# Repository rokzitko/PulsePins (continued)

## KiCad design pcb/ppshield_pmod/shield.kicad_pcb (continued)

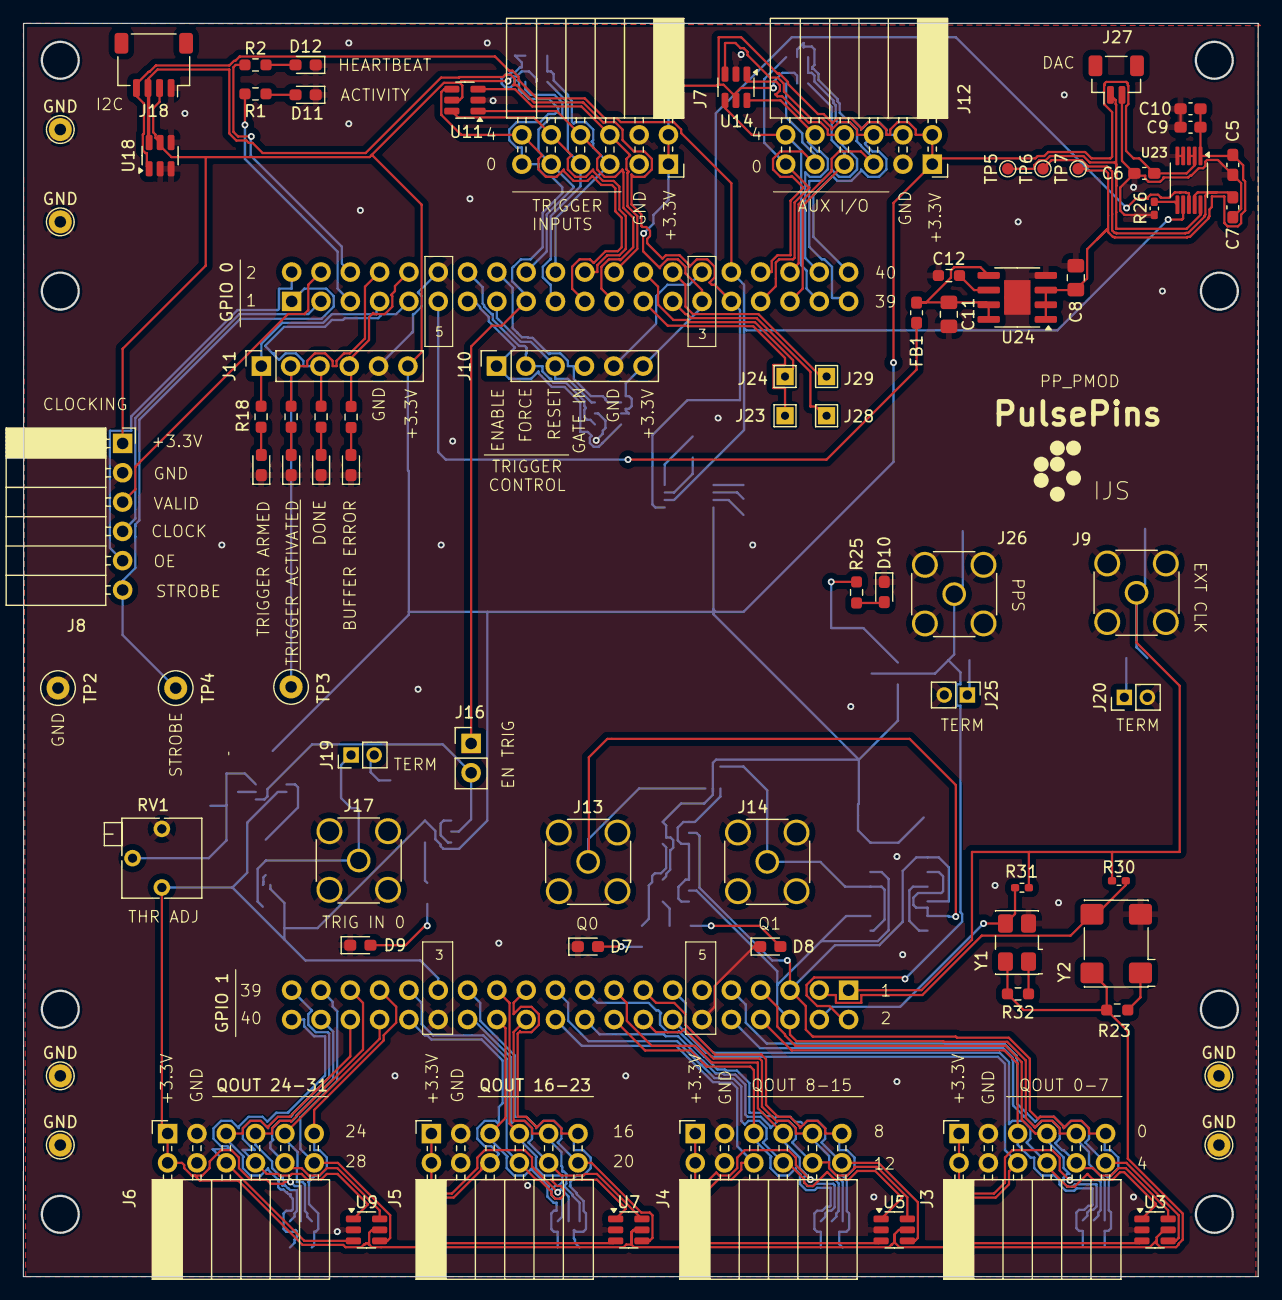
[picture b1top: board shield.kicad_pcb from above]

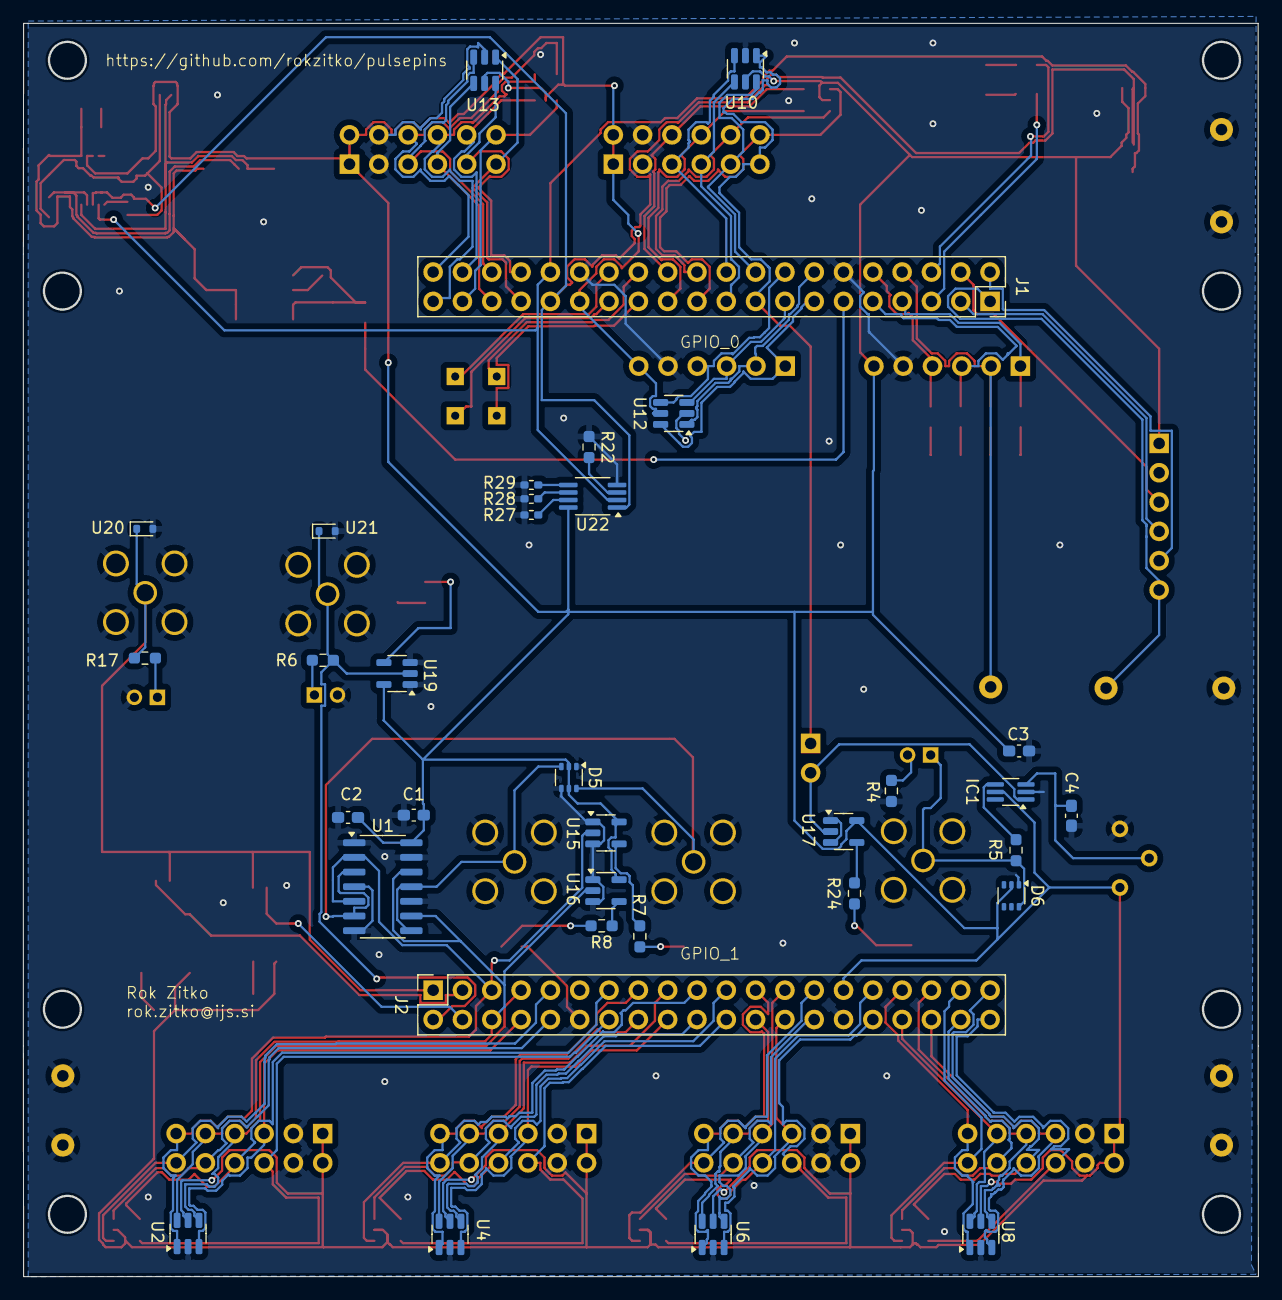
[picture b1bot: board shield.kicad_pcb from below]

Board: 2 copper layers, 107.0 x 108.6 mm, 114 parts (35 on the bottom side), 110 nets.

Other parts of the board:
GND: TestPoint; TestPoint_THTPad_D2.0mm_Drill1.0mm
GND#2, GND#3, GND#4, GND#5, GND#6: TestPoint; TestPoint_THTPad_D2.0mm_Drill1.0mm

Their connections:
GND: GND.1, GND#2.1, GND#3.1, GND#4.1, GND#5.1, GND#6.1; also elsewhere on the board

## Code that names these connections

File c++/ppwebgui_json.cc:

// SPDX-License-Identifier: MIT
// Copyright (c) 2026 Rok Zitko

#include "ppwebgui_json.hh"

#include <bitset>
#include <iomanip>
#include <sstream>

#include "combiner.hh"
#include "config.h"

namespace {

std::string bits8(const uint8_t value) {
  return std::bitset<8>(value).to_string();
}

std::string trig_bits(const uint32_t value) {
  return std::bitset<WIDTH_TRIGGER>(value & TRIGGER_MASK).to_string();
}

bool trig_enable(const uint32_t value) {
  return value & (1U << PIO1_ENABLE);
}

bool trig_force(const uint32_t value) {
  return value & (1U << PIO1_FORCE);
}

bool trig_reset(const uint32_t value) {
  return value & (1U << PIO1_RESET);
}

bool streamer_buffer_error(const uint32_t value) {
  return value & BUFFER_ERROR;
}

bool streamer_done(const uint32_t value) {
  return value & DONE;
}

bool streamer_triggered(const uint32_t value) {
  return value & TRIGGERED;
}

bool streamer_armed(const uint32_t value) {
  return value & ARMED;
}

std::string trigger_mode_to_string(const uint32_t mode) {
  switch (mode & MODE_MASK) {
  case 0: return "INT";
  case 1: return "EXT";
  case 2: return "MISC";
  case 3: return "AUX";
  case 4: return "AND";
  case 5: return "OR";
  case 6: return "XOR";
  default:
    return "UNKNOWN(" + std::to_string(mode & MODE_MASK) + ')';
  }
}

std::string trigger_mode_to_semantic_string(const TriggerConfigState &state) {
  switch (state.mode & MODE_MASK) {
  case static_cast<uint32_t>(trig_mode::INT):
    return "INT";
  case static_cast<uint32_t>(trig_mode::EXT):
    return "EXT";
  case static_cast<uint32_t>(trig_mode::MISC):
    return "MISC";
  case static_cast<uint32_t>(trig_mode::AND):
    return "ALL";
  case static_cast<uint32_t>(trig_mode::OR):
    return "ANY";
  default:
    return trigger_mode_to_string(state.mode);
  }
}

} // namespace

std::string json_escape(std::string_view input) {
  std::ostringstream out;
  for (const auto ch : input) {
    switch (ch) {
    case '\\': out << "\\\\"; break;
    case '"': out << "\\\""; break;
    case '\b': out << "\\b"; break;
    case '\f': out << "\\f"; break;
    case '\n': out << "\\n"; break;
    case '\r': out << "\\r"; break;
    case '\t': out << "\\t"; break;
    default:
      if (static_cast<unsigned char>(ch) < 0x20) {
        out << "\\u"
            << std::hex << std::uppercase << std::setw(4) << std::setfill('0')
            << static_cast<unsigned>(static_cast<unsigned char>(ch))
            << std::dec << std::nouppercase << std::setfill(' ');
      } else {
        out << ch;
      }
      break;
    }
  }
  return out.str();
}

std::string status_to_json(const StatusSnapshot &status) {
  std::ostringstream out;
  out << '{';
  out << "\"seqno\":" << status.seqno << ',';
  out << "\"poll_ms\":" << status.poll_ms << ',';
  out << "\"aux\":{";
  out << "\"raw\":" << static_cast<unsigned>(status.aux_raw) << ',';
  out << "\"bits\":\"" << bits8(status.aux_raw) << "\"},";
  out << "\"trig\":{";
  out << "\"raw\":" << status.trig_raw << ',';
  out << "\"bits\":\"" << trig_bits(status.trig_raw) << "\",";
  out << "\"enable\":" << (trig_enable(status.trig_raw) ? "true" : "false") << ',';
  out << "\"force\":" << (trig_force(status.trig_raw) ? "true" : "false") << ',';
  out << "\"reset\":" << (trig_reset(status.trig_raw) ? "true" : "false") << "},";
  out << "\"trigger_settings\":{";
  out << "\"mode\":\"" << trigger_mode_to_semantic_string(status.trigger_settings) << "\",";
  out << "\"invert_result\":" << status.trigger_settings.invert_result << ',';
  out << "\"invert_int\":" << status.trigger_settings.invert_int << ',';
  out << "\"invert_ext\":" << status.trigger_settings.invert_ext << ',';
  out << "\"invert_misc\":" << status.trigger_settings.invert_misc << ',';
  out << "\"invert_aux\":" << status.trigger_settings.invert_aux << ',';
  out << "\"mask_int\":" << status.trigger_settings.mask_int << ',';
  out << "\"mask_ext\":" << status.trigger_settings.mask_ext << ',';
  out << "\"mask_misc\":" << status.trigger_settings.mask_misc << ',';
  out << "\"mask_aux\":" << status.trigger_settings.mask_aux << "},";
  out << "\"clocking\":{";
  out << "\"tracked\":{";
  out << "\"source\":\"" << (status.clocking.tracked.source_managed ? json_escape(status.clocking.tracked.source_display) : "unmanaged") << "\",";
  out << "\"source_display\":\"" << json_escape(status.clocking.tracked.source_display) << "\",";
  out << "\"source_managed\":" << (status.clocking.tracked.source_managed ? "true" : "false") << ',';
  out << "\"core_profile\":\"" << json_escape(status.clocking.tracked.core.profile) << "\",";
  out << "\"int_profile\":\"" << json_escape(status.clocking.tracked.internal.profile) << "\"},";
  out << "\"measured\":{";
  out << "\"ext_clk_hz\":" << status.clocking.measured.ext_clk_hz << ',';
  out << "\"int_clk_hz\":" << status.clocking.measured.int_clk_hz << ',';
  out << "\"streamer_clk_hz\":" << status.clocking.measured.streamer_clk_hz << ',';
  out << "\"core_clk_hz\":" << status.clocking.measured.core_clk_hz << "}},";
  out << "\"stream\":{";
  out << "\"last_rc\":" << status.last_stream_rc << ',';
  out << "\"message\":\"" << json_escape(status.stream_message) << "\",";
  out << "\"runtime\":{";
  out << "\"raw\":" << status.streamer.status_raw << ',';
  out << "\"buffer_error\":" << (streamer_buffer_error(status.streamer.status_raw) ? "true" : "false") << ',';
  out << "\"done\":" << (streamer_done(status.streamer.status_raw) ? "true" : "false") << ',';
  out << "\"triggered\":" << (streamer_triggered(status.streamer.status_raw) ? "true" : "false") << ',';
  out << "\"armed\":" << (streamer_armed(status.streamer.status_raw) ? "true" : "false") << "}},";
  out << "\"streamer\":{";
  out << "\"status_raw\":" << status.streamer.status_raw << ',';
  out << "\"qout\":" << status.streamer.qout << ',';
  out << "\"qout_streamer\":" << status.streamer.qout_streamer << ',';
  out << "\"override\":{";
  out << "\"enabled\":" << (status.streamer.override_state.enabled ? "true" : "false") << ',';
  out << "\"value\":" << status.streamer.override_state.value << "}},";
  out << "\"combiner\":{";
  out << "\"mode\":\"" << status.combiner_mode << "\",";
  out << "\"output\":{";
  out << "\"invert\":" << status.output.invert << ',';
  out << "\"mask\":" << status.output.mask << ',';
  out << "\"force_enabled\":" << (status.output.force_enabled ? "true" : "false") << ',';
  out << "\"force_value\":" << status.output.force_value << "},";
  out << "\"inputs\":[";
  for (size_t i = 0; i < status.inputs.size(); ++i) {
    const auto &input = status.inputs[i];
    if (i) out << ',';
    out << '{';
    out << "\"index\":" << (i + 1) << ',';
    out << "\"invert\":" << input.invert << ',';
    out << "\"mask\":" << input.mask << ',';
    out << "\"force_enabled\":" << (input.force_enabled ? "true" : "false") << ',';
    out << "\"force_value\":" << input.force_value;
    out << '}';
  }
  out << "]},";
  out << "\"last_action\":\"" << json_escape(status.last_action) << "\",";
  out << "\"last_error\":\"" << json_escape(status.last_error) << "\"";
  out << '}';
  return out.str();
}

std::string operation_json(const std::string &message, const StatusSnapshot &status, const int rc) {
  std::ostringstream out;
  out << '{';
  out << "\"ok\":true,";
  out << "\"rc\":" << rc << ',';
  out << "\"message\":\"" << json_escape(message) << "\",";
  out << "\"status\":" << status_to_json(status);
  out << '}';
  return out.str();
}

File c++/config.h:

// SPDX-License-Identifier: MIT
// Copyright (c) 2025 Rok Zitko

// Constants

#pragma once

#include <cstddef>
#include <cstdint>
#include <limits>

#include "misc.hh"

constexpr int P_FIFO_IN1 = 10;
constexpr int P_FIFO_IN2 = 11;
constexpr int P_FIFO_OUT = 12;
constexpr int SIZE_FIFO_IN1 = 1 << P_FIFO_IN1;
constexpr int SIZE_FIFO_IN2 = 1 << P_FIFO_IN2;
constexpr int SIZE_FIFO_OUT = 1 << P_FIFO_OUT;
constexpr int almost_shift = 16; // see input_fifo.sv

constexpr int WIDTH_AVS_BUS = 32; // port width of the AVS bus used in the streaming interface
using bus_t = uint32_t;           // corresponding C++ type
constexpr int WIDTH_PORT = 32;    // port width in bits for various FPGA interfaces
using port_t = uint32_t;          // corresponding C++ type

static_assert(sizeof(bus_t)*8 == WIDTH_AVS_BUS);
static_assert(sizeof(port_t)*8 == WIDTH_PORT);

// These must be consistent with ip/streamer/config.vh

constexpr int WIDTH_CONTROL = 32;
constexpr int WIDTH_COUNTER = 32;
constexpr int WIDTH_DATA = 32;
constexpr int WIDTH_TOTAL = WIDTH_CONTROL + WIDTH_COUNTER + WIDTH_DATA;
constexpr int BYTES_TOTAL = WIDTH_TOTAL/8;

using control_t = uint32_t; // control register data type
using count_t   = uint32_t; // counter register data type
using value_t   = uint32_t; // value data type

static_assert(sizeof(control_t)*8 == WIDTH_CONTROL);
static_assert(sizeof(count_t)*8   == WIDTH_COUNTER);
static_assert(sizeof(value_t)*8   == WIDTH_DATA);

const uint64_t max_count_t = std::numeric_limits<count_t>::max(); // for checking boundaries

using trigger_t = uint8_t;
constexpr int WIDTH_TRIGGER = 8;
constexpr int TRIGGER_MASK = 0xFF;

using aux_t = uint8_t;
constexpr int WIDTH_AUX = 8;
constexpr int AUX_MASK = 0xFF;

constexpr uint32_t CFG_STREAMER_ACTIVE_MASK_OFFSET = 13;
constexpr uint32_t CFG_STREAMER_ARMED_LIVE_MASK_OFFSET = 17;
constexpr uint32_t STREAMER_MASK_BITS = 4;
constexpr uint32_t STREAMER_MASK_VALUE_MASK = 0x0f;
constexpr uint32_t STREAMER_ACTIVE_MASK_CFG_MASK =
  STREAMER_MASK_VALUE_MASK << CFG_STREAMER_ACTIVE_MASK_OFFSET;
constexpr uint32_t STREAMER_ARMED_LIVE_MASK_CFG_MASK =
  STREAMER_MASK_VALUE_MASK << CFG_STREAMER_ARMED_LIVE_MASK_OFFSET;

// Function aliases; we need two sets due to different interfaces (_t versions accept
// a string; those without _t suffix accept InputParse, keyword, default_value)
const auto parse_value_t = parse_uint32_t;
const auto parse_count_t = parse_uint32_t;
const auto parse_trigger_t = parse_uint8_t;
const auto parse_value = parse_uint32;
const auto parse_count = parse_uint32;
const auto parse_trigger = parse_uint8;

constexpr int PIO1_ENABLE = 8;
constexpr int PIO1_FORCE  = 9;
constexpr int PIO1_RESET  = 10;

static_assert(sizeof(trigger_t)*8 == WIDTH_TRIGGER);

// control (least significant bits):
//        0 - regular element [bit 0]
//        1 - trigger element
//       01 - trigger element (part of the sequence) [bit 1]
//       11 - trigger element (last in the sequence)
//      1x0 - sequence terminator (subtype of regular data) [bit 2]
//     1xx0 - pulses without strobes [bit 3]
// 0000xxx0 - load word [bits 4-7]
// 0001xxx0 - bit set (for bit addressing)
// 0010xxx0 - bit clear (for bit addressing)
// 0011xxx0 - bit flip (for bit addressing)
// [bit 8]  - 0=pass, 1=discard/store/replay
// [bit 9]  - store
// [bit 15] - replay
// [bit 16] - retrig
// [bit 17] - random

// These must be consistent with ip/streamer/config.vh
constexpr control_t STROBE       = 0b0000;
constexpr control_t TRIGGERBITS  = 0b0011; // mask for testing the trigger condition
constexpr control_t TRIGGER      = 0b0001;
constexpr control_t TRIGGERFINAL = 0b0010;
constexpr control_t TERMINATE    = 0b0100;
constexpr control_t NOSTROBE     = 0b1000;

constexpr control_t MODEBITS     = 0b1111'0000; // mask for testing the update mode

constexpr control_t BITLOAD      = 0b0000'0000;
constexpr control_t BITSET       = 0b0001'0000;
constexpr control_t BITCLEAR     = 0b0010'0000;
constexpr control_t BITFLIP      = 0b0011'0000;

constexpr control_t BITNOT       = 0b0100'0000;
constexpr control_t BITAND       = 0b0101'0000;
constexpr control_t BITOR        = 0b0110'0000;
constexpr control_t BITXOR       = 0b0111'0000;
constexpr control_t BITXNOR      = 0b1000'0000;

constexpr control_t BITSLL       = 0b1001'0000;
constexpr control_t BITSRL       = 0b1010'0000;

constexpr control_t PASS         = 0;
constexpr control_t NOPASS       = (1UL << 8);
constexpr control_t DISCARD      = NOPASS;
constexpr control_t STORE        = NOPASS + (1UL << 9);
constexpr control_t REPLAY       = NOPASS + (1UL << 15);
constexpr control_t RETRIG       = (1UL << 16);
constexpr control_t PRNG         = (1UL << 17);

constexpr size_t POSITIONS = 8; // number of elements that can be stored in fast memory
constexpr size_t SHIFT_POSITION = 10;
constexpr control_t POSITIONS_MASK = (0b111UL << SHIFT_POSITION);

// This must be consistent with ip/streamer/config.vh
constexpr port_t IF_CTRL       = 0b00000;
constexpr port_t INIT_VAL      = 0b00100;
constexpr port_t QOUT_OVERRIDE = 0b00110;
constexpr port_t GATING_W      = 0b00111;

constexpr port_t IF_STATUS     = 0b00000;
constexpr port_t EXT_TRIG_IN   = 0b00001;
constexpr port_t QOUT_STREAMER = 0b00010;
constexpr port_t EXT_TRIG_CTRL = 0b00011;
constexpr port_t QOUT          = 0b00100;
constexpr port_t FIFO_OVERFLOW = 0b00101;
constexpr port_t CRC32         = 0b00110;
constexpr port_t GATING_R      = 0b00111;

constexpr port_t INPUT_FIFO1_CTR_IN_L  = 0b01000;
constexpr port_t INPUT_FIFO1_CTR_IN_H  = 0b01001;
constexpr port_t INPUT_FIFO1_CTR_OUT_L = 0b01010;
constexpr port_t INPUT_FIFO1_CTR_OUT_H = 0b01011;
constexpr port_t INPUT_FIFO2_CTR_IN_L  = 0b01100;
constexpr port_t INPUT_FIFO2_CTR_IN_H  = 0b01101;
constexpr port_t INPUT_FIFO2_CTR_OUT_L = 0b01110;
constexpr port_t INPUT_FIFO2_CTR_OUT_H = 0b01111;
constexpr port_t OUTPUT_FIFO_CTR_IN_L  = 0b10000;
constexpr port_t OUTPUT_FIFO_CTR_IN_H  = 0b10001;
constexpr port_t OUTPUT_FIFO_CTR_OUT_L = 0b10010;
constexpr port_t OUTPUT_FIFO_CTR_OUT_H = 0b10011;

static_assert(GATING_W == GATING_R);

// Sanity tests
static_assert((TRIGGERBITS & TRIGGER)      == TRIGGER);
static_assert((TRIGGERBITS & TRIGGERFINAL) == TRIGGERFINAL);
static_assert((MODEBITS & BITLOAD)  == BITLOAD);
static_assert((MODEBITS & BITSET)   == BITSET);
static_assert((MODEBITS & BITCLEAR) == BITCLEAR);
static_assert((MODEBITS & BITFLIP)  == BITFLIP);

// must be consistent with ip/streamer/st_interface.sv
// status bits
constexpr port_t BUFFER_ERROR = 0x01;
constexpr port_t DONE         = 0x02;
constexpr port_t TRIGGERED    = 0x04;
constexpr port_t ARMED        = 0x08;

// control bits
constexpr port_t STOP                 = 0x01;
constexpr port_t TRIGGER_FORCE_INT    = 0x02;
constexpr port_t TRIGGER_ENABLE_INT   = 0x04;
constexpr port_t RESET                = 0x08;
constexpr port_t TRIGGER_RESET_INT    = 0x10;
constexpr port_t QOUT_SELECT          = 0x20;
constexpr port_t STOP_ON_BUFFER_ERROR = 0x40;

// bit masks for EXT_TRIG_CTRL
constexpr port_t EXT_TRIG_CTRL_ENABLE = 1<<0;
constexpr port_t EXT_TRIG_CTRL_FORCE  = 1<<1;
constexpr port_t EXT_TRIG_CTRL_RESET  = 1<<2;

// bit masks for TRIG_CTRL when combined with other signals (in combiner)
constexpr port_t TRIG_CTRL_ENABLE = 1<<(WIDTH_TRIGGER+0);
constexpr port_t TRIG_CTRL_FORCE  = 1<<(WIDTH_TRIGGER+1);
constexpr port_t TRIG_CTRL_RESET  = 1<<(WIDTH_TRIGGER+2);

// Final value when streaming terminates
constexpr value_t default_final_value = 0xFFFFFFFF;

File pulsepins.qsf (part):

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#set_location_assignment PIN_Y15 -to GPI1GPIO[0]
set_location_assignment PIN_Y15 -to EXT_CLKp
#set_location_assignment PIN_AC24 -to GPI1GPIO[1]
set_location_assignment PIN_AC24 -to PPS_IN
#set_location_assignment PIN_AA15 -to GPI1GPIO[2]
set_location_assignment PIN_AA15 -to PPCLK1
#set_location_assignment PIN_AD26 -to GPI1GPIO[3]
set_location_assignment PIN_AD26 -to PPCLK2
set_location_assignment PIN_AG28 -to GPI1Q[0] # GPI1GPIO[4]...
set_location_assignment PIN_AF28 -to GPI1Q[1]
set_location_assignment PIN_AE25 -to GPI1Q[2]
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
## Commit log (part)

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2026-04-04 path to pp for Python
2026-04-04 generalize file playback with ppplay
2026-04-04 enable binary playback and quiet parser errors
2026-04-04 standardize readback export option names
2026-04-04 prefer ppplay in docs and tests
2026-04-04 add ppplay text and binary tests
2026-04-04 document ip testbench purpose
2026-04-04 add streamer underrun testbench
2026-04-04 add streamer trigger replay test
2026-04-04 expand Python binding smoke coverage
2026-04-04 integrate counter testbenches into IP regressions
2026-04-05 installation fixes
2026-04-05 Makefile cleanup
2026-04-06 I2C OLED display test
2026-04-07 Fix ppwebgui stream playback path
2026-04-08 Return ppwebgui status in POST replies
2026-04-08 Print ppwebgui interface URLs on startup
2026-04-08 Add ppwebgui stop control
2026-04-08 ppwebgui
2026-04-08 Fix ppwebgui stream status locking
2026-04-08 Debug ppwebgui stream lock crash
2026-04-08 Externalize ppwebgui stream debug state
2026-04-08 Stabilize ppwebgui stream startup
2026-04-08 Use global stream state in ppwebgui
2026-04-08 Build ppwebgui without inlining
2026-04-08 Simplify ppwebgui verbose action logging
2026-04-08 Simplify ppwebgui to synchronous control
2026-04-08 Use local qout wrappers in ppwebgui
2026-04-09 cleanup to suppress warnings
2026-04-09 tracing support
2026-04-09 HW_DEBUG
2026-04-09 get_loc -> get_addr
2026-04-10 cleanup
2026-04-11 experimental support for updating outputs at both clock edges (DDR)
2026-04-11 give ppwebgui a fresh reset before each stream
    Run the existing bring-up path before browser-triggered streaming so each launch starts from a clean hardware state. Keep the deterministic final qout behavior aligned with the manual reset flow.
2026-04-11 clarify ppwebgui live vs tracked interface state
    Split the browser UI into live-hardware and ppwebgui-tracked sections so snapshot-backed values stop reading like live hardware state. Surface unapplied local edits in the override and combiner forms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
2026-04-12 add shared ppwebgui value type definitions
    Introduce a dedicated header for the value structs shared across ppwebgui so later separation work can stop mixing request/status data models with the rest of the web server implementation.
2026-04-12 add stable ppwebgui service interface adapter
    Route ppwebgui through a value-based service interface without moving or re-owning the hardware controller object. Keep the WebGuiController instance anchored in main and let the adapter hold only a 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
2026-04-12 extract ppwebgui json presentation helpers
    Move JSON encoding and status presentation helpers out of ppwebgui.cc so response rendering can evolve independently of the main server/bootstrap file. Keep the HTTP behavior and hardware-control own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
2026-04-12 split ppwebgui runtime config from input parsing
    Resolve ppwebgui startup and policy settings into a pure WebGuiRuntimeConfig in main, then pass that config into the anchored controller instead of storing the raw InputParser. Keep the hardware-owni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
2026-04-12 extract ppwebgui app composition
    Move the ppwebgui composition block out of the main file while keeping the hardware-owning controller anchored as a direct local in the app runner. This keeps ppwebgui.cc focused on process entry and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
2026-04-12 decouple ppwebgui app runner from host runtime
    Resolve the pure WebGuiRuntimeConfig in ppwebgui_main.cc and pass only FPGA, Verbosity, and the resolved config into the app runner. Keep the hardware controller anchored in the app layer while remov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
2026-04-12 make ppwebgui server depend on explicit assets
    Pass a pure WebGuiAssets bundle from the app layer into the server runner so the server module no longer reaches into asset globals directly. This keeps the controller lifetime unchanged while making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
2026-04-12 centralize ppwebgui frontend boundary types
    Collect the remaining pure GUI/server boundary structs into a single frontend header and update the server and HTTP layers to consume those values explicitly. Refresh the maintainer docs so the final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
2026-04-12 document final ppwebgui architecture split
    Update the maintainer docs to reflect the completed ppwebgui layering, control flow, and pure-value boundaries between the app, server, HTTP, and hardware-owning service layers. Record the anchored W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
2026-04-12 add backend trigger updates for ppwebgui
    Add a pure trigger configuration request type, service/controller apply path, and POST /api/trigger so ppwebgui can update trigger settings through the split backend architecture. Preserve AUX trigge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
2026-04-12 document editable trigger settings in ppwebgui
    Update the ppwebgui docs to describe the new trigger editing flow, the semantic trigger modes exposed in the browser, and the POST /api/trigger endpoint. Clarify that AUX trigger fields remain visibl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
2026-04-13 add ppwebgui clocking controls
    Expose tracked clock source and PLL profile settings in the browser, along with measured ext/int/streamer/core frequency snapshots and a remeasure action. Reuse the existing dirty/apply/revert form b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
2026-04-13 fix clocking + reduce verbosity
2026-04-13 harden ppscpi session handling and shutdown semantics
    Contain SCPI handler exceptions inside the generic session layer so malformed or failing commands stop affecting only the current request instead of tearing down the whole server. Add explicit DISCON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
2026-04-15 harden host startup and input parsing
    Reject malformed numeric arguments deterministically, fail fast on invalid raw clock selection, and surface startup compatibility errors instead of relying on asserts or uncaught exceptions.
2026-04-16 fix RC codes to make them unique
2026-04-16 sh -> bash
2026-04-17 harden timeout handling and web recovery
2026-04-17 add AD9833 SPI payload target
    Split the standalone SPI payload generator around a shared 32-bit encoder so the new 5 MHz AD9833 sequence can drive qout[16..19] without breaking the existing PMODDA3 binary.
2026-04-17 add AD9833 amplifier payload target
    Add an MCP41010 helper and a third spi_payload binary so the DollaTek module can be programmed for the same 5 MHz AD9833 setup plus the board's approximate 5x amplified-output stage from one generate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
2026-04-17 flatten element storage
    Store raw control/count/value fields inside el instead of shared wrapper objects while preserving the existing constructor surface and semantic behavior covered by the unit tests.
2026-04-17 sync element mode metadata
    Replace RTTI-based wrapper classification with explicit kind tags and resynchronize cached regular-mode semantics when control bits change, backed by regression tests for setter behavior.
2026-04-17 share element control decoding
    Centralize raw control-word and trigger-field decoding in el so binary reconstruction and text serialization reuse the same helper logic, with regression tests covering the shared decoders.
2026-04-17 add immutable element transforms
    Replace the last setter choreography with immutable el helpers, derive element kind from control, and centralize regular token parsing so sequence reconstruction and text conversion share the same ru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
2026-04-20 align Python element bindings
    Update the Python bindings, tests, and docs to the flattened el API, add the missing retrig/prng surface, and make the board-side test fixture tolerate frequency-meter layouts that do not expose the 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
2026-04-20 tighten include hygiene
    Add missing direct includes and drop clearly unused ones in the audited project-owned C++ sources so core headers, tools, and bindings rely less on transitive includes.
2026-04-20 hps_0.h for CI
2026-04-20 pregenerated hps_0.h
2026-04-20 one more
2026-04-20 add worked examples guide
    Replace the examples roadmap with concrete PulsePins workflows that show exact commands, expected behavior, and links to the detailed tool pages for common bring-up and lab tasks.
2026-04-20 add extension cookbook
    Document the concrete file-by-file extension paths for new CLI tools, Python bindings, sequence constructs, tests, and ppwebgui features so contributors can add functionality without reverse-engineer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
2026-04-20 split Python bindings across translation units
2026-04-20 fix exclusion
2026-04-21 add board smoke automation
2026-04-21 expand board smoke failure coverage
2026-04-21 report ppscpi failures in error queue
2026-04-22 polish docs landing and dev workflow
    Turn the docs front door into a hardware-first guide, upgrade the weakest command pages, add a unified host-side dev-check target, and align CI and testing docs around dev-check, board-smoke, and run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
2026-04-29 add option to skip forever test reports
2026-04-29 add browser timeline composer
2026-04-30 add timeline draft import export
2026-04-30 add timeline preview click insertion
2026-04-30 add timeline pulse selection controls
2026-04-30 add timeline selection keyboard shortcuts
2026-04-30 list ppwebgui interface addresses
2026-04-30 add host-side timeline builder
2026-04-30 add timeline draft json roundtrip
2026-04-30 add ppscpi clock workflow helpers
2026-05-23 rstmgr as part of class fpga
2026-05-26 dark_mode
2026-06-05 move version check into FPGA
2026-06-05 fix servo PWM duty units
2026-06-06 fix ppfreq sample count
2026-06-06 use RAII cout locking
2026-06-06 replace runtime asserts with exceptions
2026-06-06 add loc address constructors
2026-06-06 make random final output explicit
2026-06-06 validate numeric timing inputs
2026-06-06 avoid narrowing ppfreq count
2026-06-07 gate quartus timing checks
2026-06-07 refresh ppfreq streamer clock cache
2026-06-07 hide inactive readback mode
2026-06-07 remove stale ppwebgui workaround note
2026-06-07 resolve quartus tools from qdir
2026-06-07 cover omitted ip test benches
2026-06-07 document rtl latency behavior
2026-06-07 clarify reset behavior in docs
2026-06-07 fix qsys component dependencies
2026-06-07 clean third party c++ artifacts
2026-06-07 update timestamp timeout test
2026-06-23 standardize return codes
2026-06-23 refresh tool documentation
2026-06-23 explain FPGA build artifacts
2026-06-23 link ppread and ppplay docs
2026-06-23 link Avalon documentation resources
2026-06-23 document CRC32 integrity checks
2026-06-23 quick edit
2026-06-23 link Qwiic documentation resources
2026-06-23 remove historical documentation wording
2026-06-24 link ISO 8601 documentation resources
2026-06-24 minor fixes
2026-06-24 link related documentation pages
2026-06-24 fix markdown list indentation
2026-06-24 fix documentation typos
2026-06-25 more docs fixes
2026-06-25 ppscpi vs. pptool -server disambiguation in recipes
2026-06-25 ppfg -gate recipe fix
2026-06-25 Respect explicit ppfg timing in servo mode
2026-06-25 Align counter correlation report depth
2026-06-25 Add hard readback timeout and ppfreq format
2026-06-26 Fix RTL edge cases and testbenches
2026-06-26 Redesign streamer CDC crossings
2026-06-26 Fix CDC helper Questa compile
2026-06-27 Fix split-clock QOUT readback test
2026-06-27 Fix playback and docs consistency
2026-06-27 Fix force trigger readiness wait
2026-06-27 Add ppts timestamp overflow ignore option
2026-06-27 Fix warning-reported C++ issues
2026-06-27 Bump release and FPGA ABI versions
2026-06-27 Fix readback FIFO element readiness
2026-06-27 Fix no-strobe qout updates
2026-06-28 bash + error propagation + small fixes
2026-06-28 Default trigger mode to internal
2026-06-28 minor fix
2026-06-28 Fix streamer timing and overflow handling
2026-06-28 Fix counter edge cases
2026-06-28 Fix streamer decoder pacing
2026-06-28 Fix readback and timestamp edge cases
2026-06-28 Fix CDC and streamer config sequencing
2026-06-28 Fix test runner failure reporting
2026-06-29 Fix ppwebgui trigger and HTTP guards
2026-06-29 test improvements
2026-06-29 missing file
2026-06-29 Fix boot copy and hardware check errors
2026-06-30 remove combiner_trig modes that are actually not implemented, and not intended to be implemented
2026-06-30 Reject non-terminal final records
2026-06-30 Add streamer timing diagrams
2026-06-30 Fix streamer PRNG state tracking
2026-06-30 reverse order
